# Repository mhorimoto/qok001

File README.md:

# 色々なサンプル

ロジックICを使ってArduinoやXPiをもっと楽しく使う手法を考える会的回路。

001 - 入力ピンが多くて大変な時に上手に入力ピン数を少なくする方法としてのエンコーダ
　　　ただし、同時入力には難ありだけどね。
参考URL https://toshiba.semicon-storage.com/jp/semiconductor/product/general-purpose-logic-ics/detail.TC74HC148AP.html

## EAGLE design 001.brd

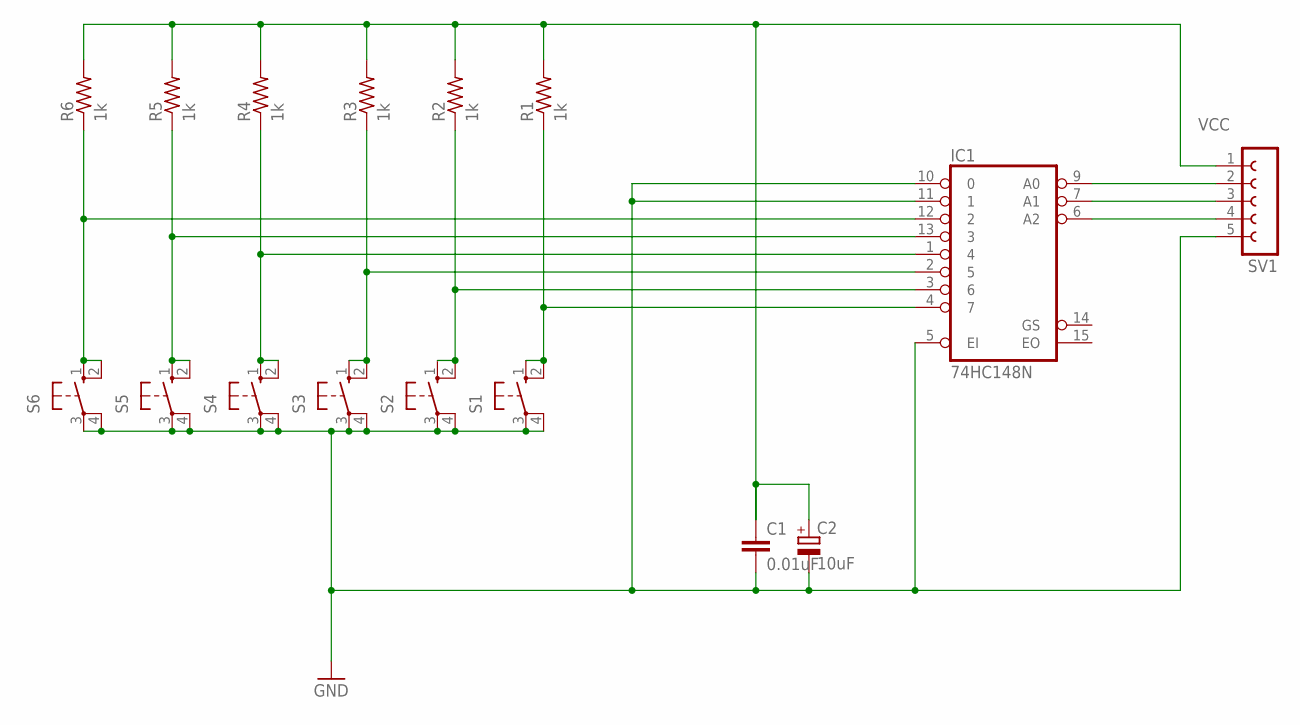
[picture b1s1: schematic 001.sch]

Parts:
C1: 0.01uF; C025-025X050
C2: 10uF; E2,5-6E
IC1: 74HC148N; DIL16
R1, R2, R3, R4, R5, R6: 1k; 0207/7
S1, S2, S3, S4, S5, S6: 10-XX; B3F-10XX
SV1: FE05-1

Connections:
GND: C1.2, C2.-, IC1.5 (EI), IC1.8 (GND), IC1.10 (0), IC1.11 (1), S1.3, S1.4 (P1), S2.3, S2.4 (P1), S3.3, S3.4 (P1), S4.3, S4.4 (P1), S5.3, S5.4 (P1), S6.3, S6.4 (P1), SV1.5
unnamed: IC1.4 (7), R1.1, S1.1 (S), S1.2 (S1)
unnamed: IC1.3 (6), R2.1, S2.1 (S), S2.2 (S1)
unnamed: IC1.2 (5), R3.1, S3.1 (S), S3.2 (S1)
unnamed: IC1.1 (4), R4.1, S4.1 (S), S4.2 (S1)
unnamed: IC1.13 (3), R5.1, S5.1 (S), S5.2 (S1)
unnamed: IC1.12 (2), R6.1, S6.1 (S), S6.2 (S1)
unnamed: IC1.9 (A0), SV1.2
unnamed: IC1.7 (A1), SV1.3
unnamed: IC1.6 (A2), SV1.4
VCC: C1.1, C2.+, IC1.16 (VCC), R1.2, R2.2, R3.2, R4.2, R5.2, R6.2, SV1.1

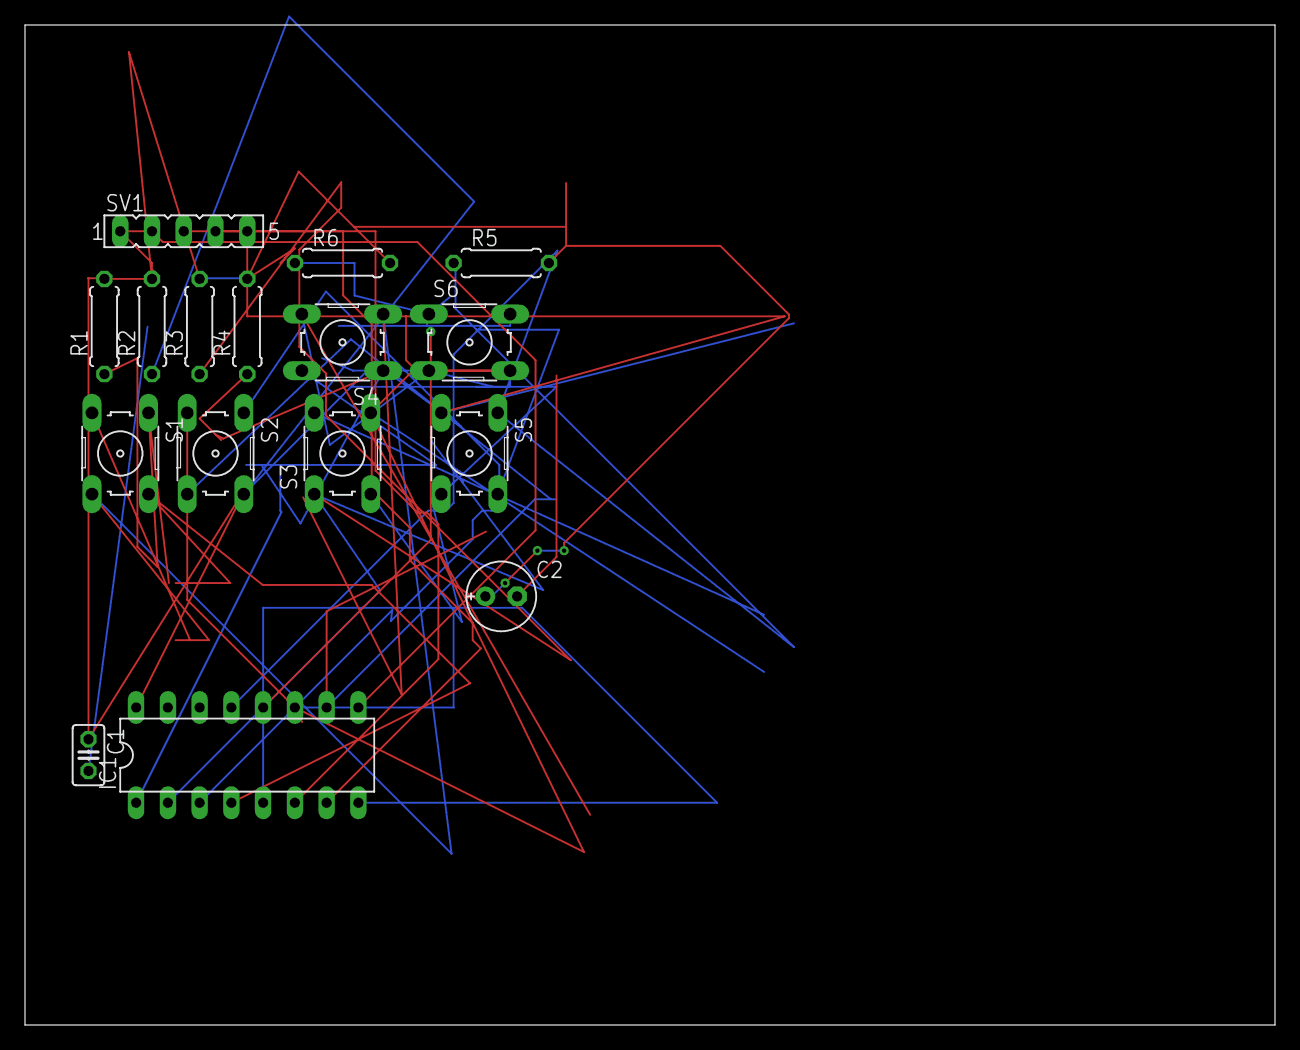
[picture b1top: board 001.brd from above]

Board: 2 copper layers, 100.0 x 80.0 mm, 16 parts (0 on the bottom side), 11 nets.

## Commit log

2020-06-12 001の途中。PCBデザイン中
2020-06-14 PCB パターンそれなりに完成
